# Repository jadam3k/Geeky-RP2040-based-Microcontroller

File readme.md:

### Info about traces ;))
I think they are good im not making f35 controler so i can go with that ;)

# Geeky - RP2040 Microcontroller Project

**Geeky** is an RP2040-based microcontroller board. I created this project to dive deeper into microcontroller design. Because of that, the board is slightly larger than typical designs.  

I wanted to solder everything myself, which made assembling the MCU quite a challenge—but also a great learning experience.  

Below you can find the 3D model, schematic, board layout, and the bill of materials (BOM).

---

## Design Overview

- **Board Type:** RP2040 Microcontroller
- **Focus:** Learning low-level MCU operation and manual soldering
- **Size:** Slightly larger than standard microcontroller boards to accommodate manual assembly

### 3D Model, Schematic, and Layout

---

## Bill of Materials (BOM)

| Designator         | Footprint                               | Quantity | Item Name                               | Price (USD) | All Cost (USD) |
|-------------------|----------------------------------------|---------|----------------------------------------|------------|----------------|
| C1, C2, C3, C4    | 805                                    | 4       | 1uF Capacitor                           | 1.43       | 28.80          |
| C5, C6, C7, C8    | 805                                    | 8       | 100nF Capacitor                          | 1.63       | 28.80          |
| C13, C14          | 805                                    | 2       | 18pF Capacitor                            | 2.93       | 28.80          |
| C15, C16, C17     | 805                                    | 3       | 10uF Capacitor                            | 1.42       | 28.80          |
| J1                | USB_C_Receptacle_HRO_TYPE-C-31-M-12   | 1       | USB-C Receptacle                          | 1.74       | 28.80          |
| J2                | PinHeader_2x03_P2.54mm_Vertical       | 1       | DEBUG Header                              | 2.08       | 28.80          |
| J3, J4            | PinHeader_1x20_P2.54mm_Vertical       | 2       | 1x20 Connector                            | 1.44       | 28.80          |
| R1, R2, R3, R4, R5| 805                                    | 5       | Resistor (27Ω SMD, best price)           | 3.39       | 28.80          |
| SW1               | SW_Push_SPST_NO_Alps_SKRK             | 1       | Push Button Switch                        | 0.46       | 28.80          |
| SW2               | SW_Push_SPST_NO_Alps_SKRK             | 1       | BOOTSEL Button                            | 0          | 28.80          |
| U1                | QFN-56-1EP_7x7mm_P0.4mm_EP3.2x3.2mm   | 1       | RP2040 Microcontroller                     | 4.28       | 28.80          |
| U2                | SOT-223-3_TabPin2                      | 1       | AMS1117-3.3 Voltage Regulator             | 0.70       | 28.80          |
| U3                | SOIC-8_5.3x5.3mm_P1.27mm               | 1       | W25Q128JVS Flash Memory                    | 5.49       | 28.80          |
| Y1                | Crystal_SMD_5032-4Pin_5.0x3.2mm       | 1       | 12MHz Crystal                              | 1.81       | 28.80          |

**Total Cost (with shipping): $42.50**

---

This project is a perfect example for anyone looking to get hands-on experience with microcontrollers and manual soldering. The RP2040 opens the door to countless learning possibilities, and building it yourself makes the knowledge stick.

##How to use 
# Flashing Code to RP2040 Using Arduino IDE Without Downloads

## Requirements
- **Arduino IDE** installed
- **RP2040 board** (e.g., Raspberry Pi Pico)
- **W25Q128JVS Flash Memory** connected

## Instructions

1. **Connect the RP2040 to Your Computer.**
   - Use a USB cable to connect your RP2040 board to your PC.

2. **Open Arduino IDE.**

3. **Select Your Board.**
   - Go to **Tools > Board** and choose **Raspberry Pi Pico** or your specific RP2040 board.

4. **Select the Correct Port.**
   - Navigate to **Tools > Port** and choose the COM port that corresponds to your RP2040.

5. **Write Your Code.**
   - Use the code below to read and write to the W25Q128JVS Flash:

```cpp
#include <SPI.h>

#define CS\_PIN 5  // Chip Select pin

void setup() {
    Serial.begin(9600);
    SPI.begin();
    pinMode(CS\_PIN, OUTPUT);
    digitalWrite(CS\_PIN, HIGH);  // Deselect the flash
}

void loop() {
    writeFlash(0x000000, "Hello");
    delay(1000);

    char data[6] = {0};
    readFlash(0x000000, data, 5);
    data[5] = '\0';  // Null-terminate the string
    Serial.println(data);  // Print the data
    delay(2000);
}

void writeFlash(uint32\_t address, const char* data) {
    digitalWrite(CS\_PIN, LOW);
    SPI.transfer(0x06);  // Write Enable
    digitalWrite(CS\_PIN, HIGH);

    digitalWrite(CS\_PIN, LOW);
    SPI.transfer(0x02);  // Page Program
    SPI.transfer((address >> 16) & 0xFF);  // Address byte 1
    SPI.transfer((address >> 8) & 0xFF);   // Address byte 2
    SPI.transfer(address & 0xFF);          // Address byte 3
    for (int i = 0; i < 5; i++) {
        SPI.transfer(data[i]);  // Send data
    }
    digitalWrite(CS\_PIN, HIGH);
}

void readFlash(uint32\_t address, char* buffer, size\_t length) {
    digitalWrite(CS\_PIN, LOW);
    SPI.transfer(0x03);  // Read Data
    SPI.transfer((address >> 16) & 0xFF);  // Address byte 1
    SPI.transfer((address >> 8) & 0xFF);   // Address byte 2
    SPI.transfer(address & 0xFF);          // Address byte 3
    for (size\_t i = 0; i < length; i++) {
        buffer[i] = SPI.transfer(0x00);  // Read data
    }
    digitalWrite(CS\_PIN, HIGH);
}

``` 
-Upload the Code.
> Click the Upload button (the arrow icon) in the Arduino IDE to upload your code to the RP2040.

-Open Serial Monitor.
> After uploading, open the Serial Monitor (set to 9600 baud) to see the output from the Flash memory.

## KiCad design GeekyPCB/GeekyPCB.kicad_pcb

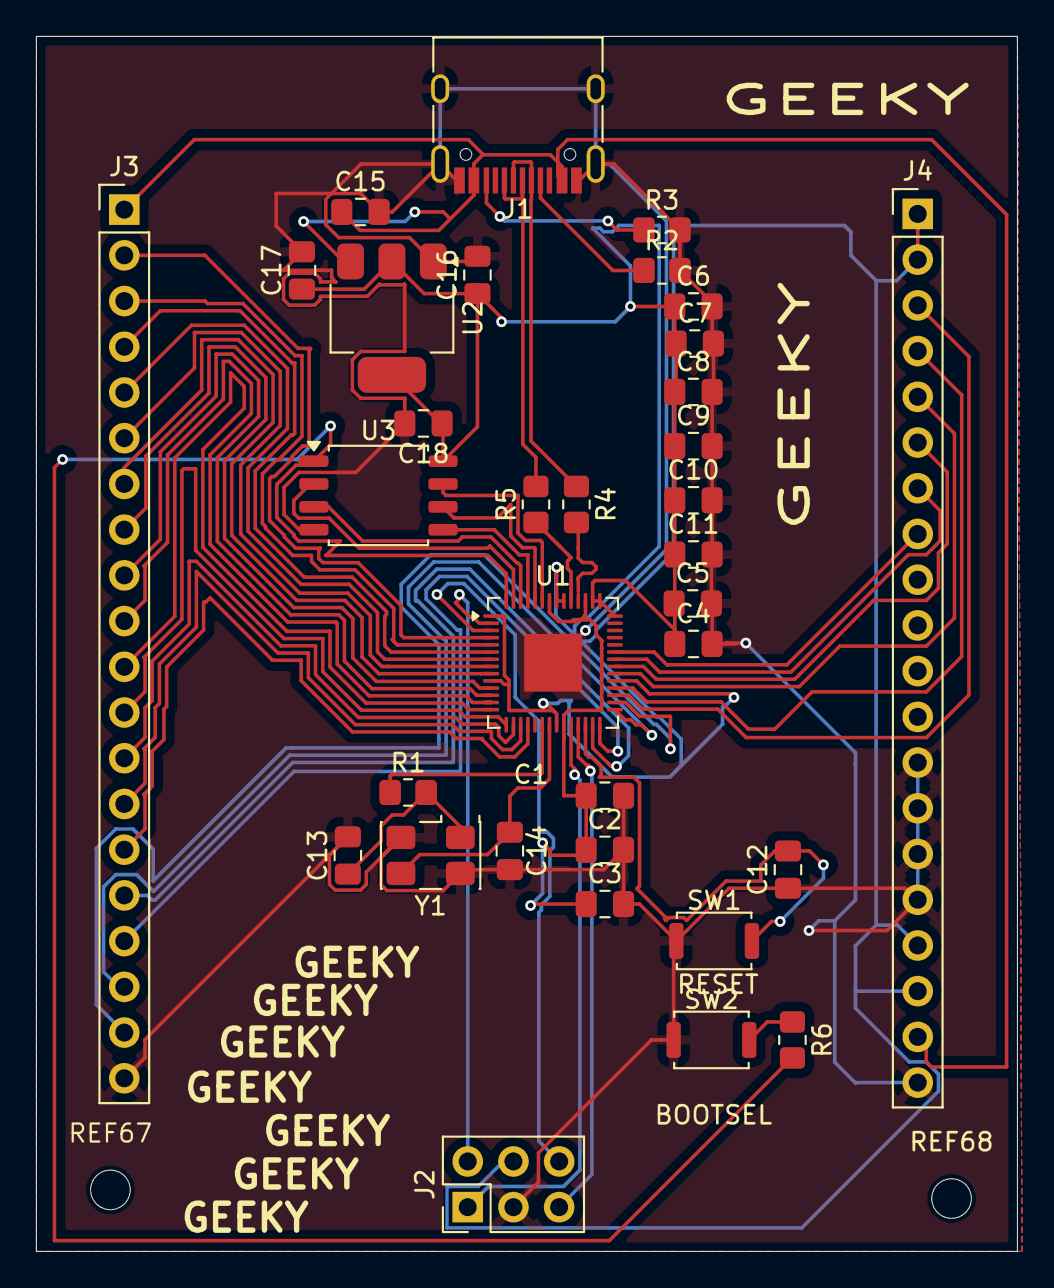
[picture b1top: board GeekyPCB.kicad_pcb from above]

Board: 2 copper layers, 54.5 x 67.5 mm, 36 parts (0 on the bottom side), 49 nets.

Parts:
C1, C2, C3, C4: 1uF; C_0805_2012Metric_Pad1.18x1.45mm_HandSolder
C5, C6, C7, C8, C9, C10, C11, C12, C18: 100nF; C_0805_2012Metric_Pad1.18x1.45mm_HandSolder
C13, C14: 18pF; C_0805_2012Metric_Pad1.18x1.45mm_HandSolder
C15, C16, C17: 10uF; C_0805_2012Metric_Pad1.18x1.45mm_HandSolder
J1: USB_C_Receptacle_USB2.0_14P; USB_C_Receptacle_HRO_TYPE-C-31-M-12
J2: DEBUG; PinHeader_2x03_P2.54mm_Vertical
J3, J4: Conn_01x20; PinHeader_1x20_P2.54mm_Vertical
R1, R6: 1k; R_0805_2012Metric_Pad1.20x1.40mm_HandSolder
R2, R3: 5.1k; R_0805_2012Metric_Pad1.20x1.40mm_HandSolder
R4, R5: 27; R_0805_2012Metric_Pad1.20x1.40mm_HandSolder
REF67, REF68: MountingHole_2.2mm_M2
SW1: SW_Push; SW_Push_SPST_NO_Alps_SKRK
SW2: BOOTSEL; SW_Push_SPST_NO_Alps_SKRK
U1: RP2040; QFN-56-1EP_7x7mm_P0.4mm_EP3.2x3.2mm
U2: AMS1117-3.3; SOT-223-3_TabPin2
U3: W25Q128JVS; SOIC-8_5.3x5.3mm_P1.27mm
Y1: 12MHz; Crystal_SMD_5032-4Pin_5.0x3.2mm

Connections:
+1V1: C1.1, C2.1, C3.1, U1.23 (DVDD), U1.45 (VREG_VOUT), U1.50 (DVDD)
+3.3V: C4.1, C5.1, C6.1, C7.1, C8.1, C9.1, C10.1, C11.1, C16.1, C17.1, C18.1, J2.4, J4.1, J4.2, J4.17, J4.18, U1.1 (IOVDD), U1.10 (IOVDD), U1.22 (IOVDD), U1.33 (IOVDD), U1.42 (IOVDD), U1.43 (ADC_AVDD), U1.44 (VREG_VIN), U1.48 (USB_VDD), U1.49 (IOVDD), U2.2 (VO), U3.8 (VCC)
+5V: C15.1, J1.A4 (VBUS), J1.A9 (VBUS), J1.B4 (VBUS), J1.B9 (VBUS), J3.1, J4.19, U2.3 (VI)
CC1: J1.A5 (CC1), R2.1
CC2: J1.B5 (CC2), R3.1
D+: J1.A6 (D+), J1.B6 (D+), R5.2
D-: J1.A7 (D-), J1.B7 (D-), R4.1
GND: C1.2, C2.2, C3.2, C4.2, C5.2, C6.2, C7.2, C8.2, C9.2, C10.2, C11.2, C12.1, C13.2, C14.2, C15.2, C16.2, C17.2, C18.2, J1.A1 (GND), J1.A12 (GND), J1.B1 (GND), J1.B12 (GND), J1.S1 (SHIELD), J2.3, J3.20, J4.13, J4.14, J4.15, J4.16, J4.20, R2.2, R3.2, SW1.1, SW2.1, U1.57 (GND), U2.1 (GND), U3.4 (GND), Y1.2 (G), Y1.4 (G)
GPIO2: J3.2, U1.4 (GPIO2)
GPIO3: J3.3, U1.5 (GPIO3)
GPIO4: J3.4, U1.6 (GPIO4)
GPIO5: J3.5, U1.7 (GPIO5)
GPIO6: J3.6, U1.8 (GPIO6)
GPIO7: J3.7, U1.9 (GPIO7)
GPIO8: J3.8, U1.11 (GPIO8)
GPIO9: J3.9, U1.12 (GPIO9)
GPIO10: J3.10, U1.13 (GPIO10)
GPIO11: J3.11, U1.14 (GPIO11)
GPIO12: J3.12, U1.15 (GPIO12)
GPIO13: J3.13, U1.16 (GPIO13)
GPIO14: J3.14, U1.17 (GPIO14)
GPIO15: J3.15, U1.18 (GPIO15)
GPIO16: J3.16, U1.27 (GPIO16)
GPIO17: J3.17, U1.28 (GPIO17)
GPIO18: J3.18, U1.29 (GPIO18)
GPIO19: J3.19, U1.30 (GPIO19)
GPIO20: J4.3, U1.31 (GPIO20)
GPIO21: J4.4, U1.32 (GPIO21)
GPIO22: J4.5, U1.34 (GPIO22)
GPIO23: J4.6, U1.35 (GPIO23)
GPIO24: J4.7, U1.36 (GPIO24)
GPIO25: J4.8, U1.37 (GPIO25)
unnamed: C13.1, R1.2, Y1.1
unnamed: R6.1, SW2.2
unnamed: C12.2, SW1.2, U1.26 (RUN)
unnamed: R4.2, U1.46 (USB_DM)
unnamed: R5.1, U1.47 (USB_DP)
QSPI_SCLK: U1.52 (QSPI_SCLK), U3.6 (CLK)
QSPI_SD0: U1.53 (QSPI_SD0), U3.5 (DI/IO_{0})
QSPI_SD1: U1.55 (QSPI_SD1), U3.2 (DO/IO_{1})
QSPI_SD2: U1.54 (QSPI_SD2), U3.3 (~WP/IO_{2})
QSPI_SD3: U1.51 (QSPI_SD3), U3.7 (~HOLD/~RESET/IO_{3})
QSPI_SS: R6.2, U1.56 (~QSPI_SS), U3.1 (~CS)
RX0: J2.6, U1.3 (GPIO1)
SWCLK: J2.1, U1.24 (SWCLK)
SWD: J2.5, U1.25 (SWDIO)
TX0: J2.2, U1.2 (GPIO0)
X0: C14.1, U1.21 (XOUT), Y1.3
XI: R1.1, U1.20 (XIN)

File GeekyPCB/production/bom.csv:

Designator,Footprint,Quantity,Value,LCSC Part #
"C1, C2, C3, C4",0805,4,1uF,
"C10, C11, C12, C18, C5, C6, C7, C8, C9",0805,9,100nF,
"C13, C14",0805,2,18pF,
"C15, C16, C17",0805,3,10uF,
J1,USB_C_Receptacle_HRO_TYPE-C-31-M-12,1,USB_C_Receptacle_USB2.0_14P,
J2,PinHeader_2x03_P2.54mm_Vertical,1,DEBUG,
"J3, J4",PinHeader_1x20_P2.54mm_Vertical,2,Conn_01x20,
"R1, R6",0805,2,1k,
"R2, R3",0805,2,5.1k,
"R4, R5",0805,2,27,
SW1,SW_Push_SPST_NO_Alps_SKRK,1,SW_Push,
SW2,SW_Push_SPST_NO_Alps_SKRK,1,BOOTSEL,
U1,QFN-56-1EP_7x7mm_P0.4mm_EP3.2x3.2mm,1,RP2040,
U2,SOT-223-3_TabPin2,1,AMS1117-3.3,
U3,SOIC-8_5.3x5.3mm_P1.27mm,1,W25Q128JVS,
Y1,Crystal_SMD_5032-4Pin_5.0x3.2mm,1,12MHz,

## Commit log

2026-02-19 final
2026-02-19 Dodane pliki
